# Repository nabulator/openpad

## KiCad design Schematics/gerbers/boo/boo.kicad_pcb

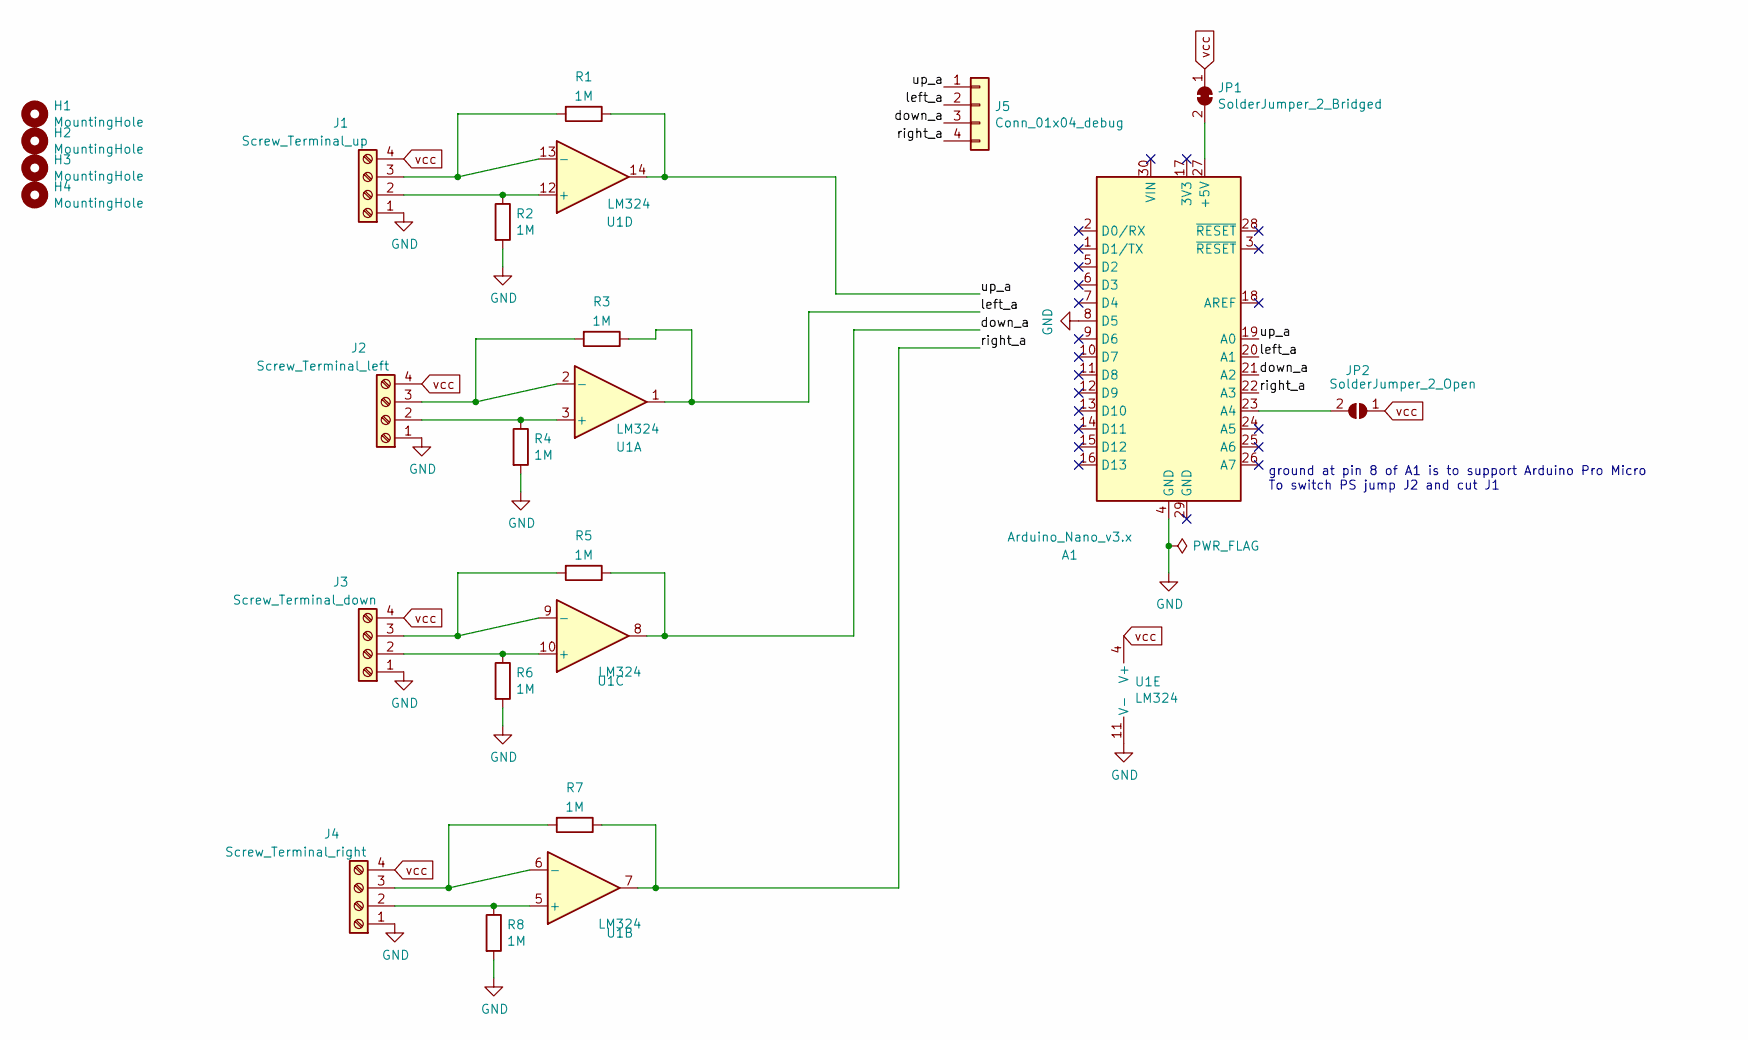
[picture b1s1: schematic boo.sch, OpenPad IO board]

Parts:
A1: Arduino_Nano_v3.x; Arduino_Nano_WithMountingHoles
H1, H2, H3, H4: MountingHole; MountingHole_6.4mm_M6
J1: Screw_Terminal_up; PinHeader_1x04_P2.54mm_Vertical
J2: Screw_Terminal_left; PinHeader_1x04_P2.54mm_Vertical
J3: Screw_Terminal_down; PinHeader_1x04_P2.54mm_Vertical
J4: Screw_Terminal_right; PinHeader_1x04_P2.54mm_Vertical
J5: Conn_01x04_debug; JST_XH_B4B-XH-A_1x04_P2.50mm_Vertical
JP1: SolderJumper_2_Bridged; SolderJumper-2_P1.3mm_Bridged2Bar_Pad1.0x1.5mm
JP2: SolderJumper_2_Open; SolderJumper-2_P1.3mm_Open_Pad1.0x1.5mm
R1, R2, R3, R4, R5, R6, R7, R8: 1M; R_Axial_DIN0207_L6.3mm_D2.5mm_P10.16mm_Horizontal
U1: LM324; DIP-14_W7.62mm_Socket

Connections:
/down_a: A1.21 (A2), J5.3, R5.1, U1.8
/left_a: A1.20 (A1), J5.2, R3.1, U1.1
/right_a: A1.22 (A3), J5.4, R7.1, U1.7
/up_a: A1.19 (A0), J5.1, R1.1, U1.14
GND: A1.4 (GND), A1.8 (D5), J1.1, J2.1, J3.1, J4.1, R2.2, R4.2, R6.2, R8.2, U1.11 (V-)
unnamed: A1.23 (A4), JP2.2 (B)
unnamed: A1.27 (+5V), JP1.2 (B)
unnamed: J1.2, R2.1, U1.12 (+)
unnamed: J1.3, R1.2, U1.13 (-)
unnamed: J2.2, R4.1, U1.3 (+)
unnamed: J2.3, R3.2, U1.2 (-)
unnamed: J3.2, R6.1, U1.10 (+)
unnamed: J3.3, R5.2, U1.9 (-)
unnamed: J4.2, R8.1, U1.5 (+)
unnamed: J4.3, R7.2, U1.6 (-)
vcc: J1.4, J2.4, J3.4, J4.4, JP1.1 (A), JP2.1 (A), U1.4 (V+)

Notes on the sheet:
ground at pin 8 of A1 is to support Arduino Pro Micro To switch PS jump J2 and cut J1

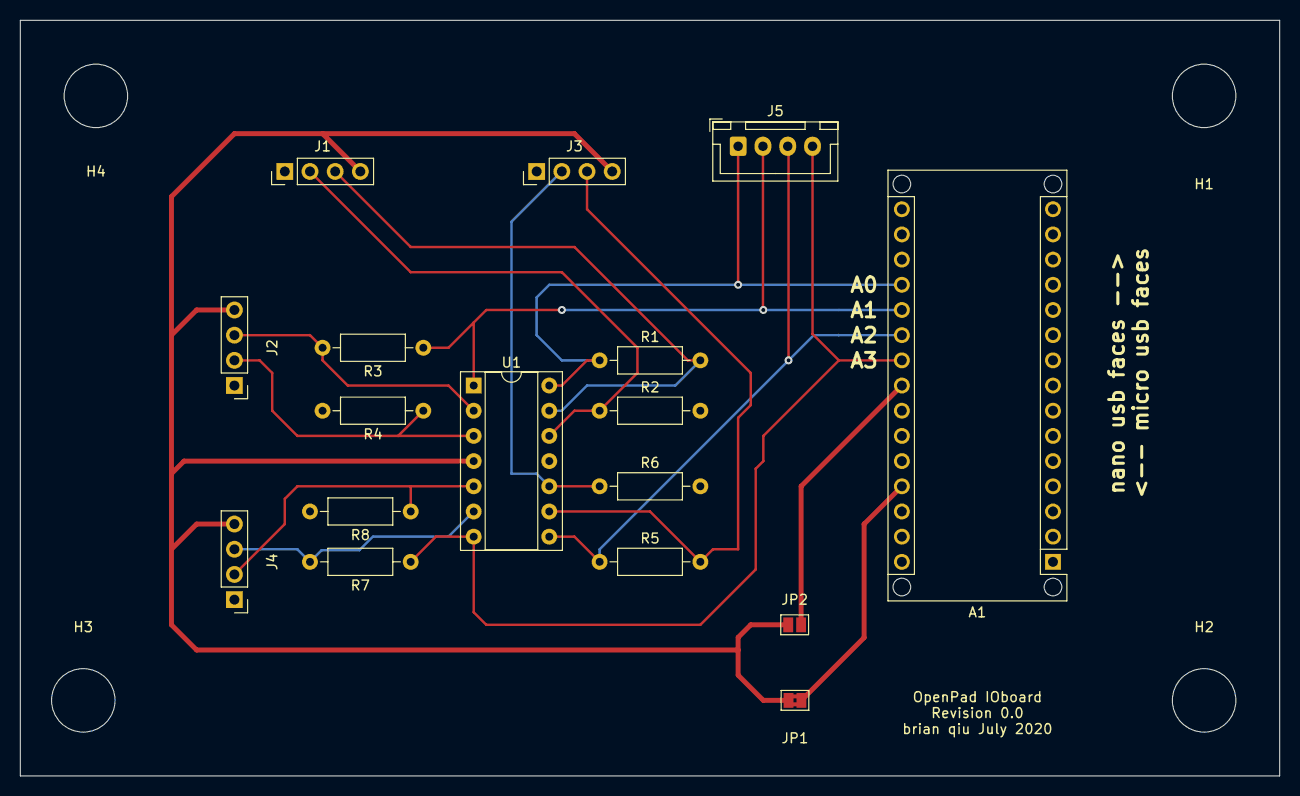
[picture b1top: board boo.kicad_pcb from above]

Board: 2 copper layers, 127.0 x 76.2 mm, 21 parts (0 on the bottom side), 16 nets.

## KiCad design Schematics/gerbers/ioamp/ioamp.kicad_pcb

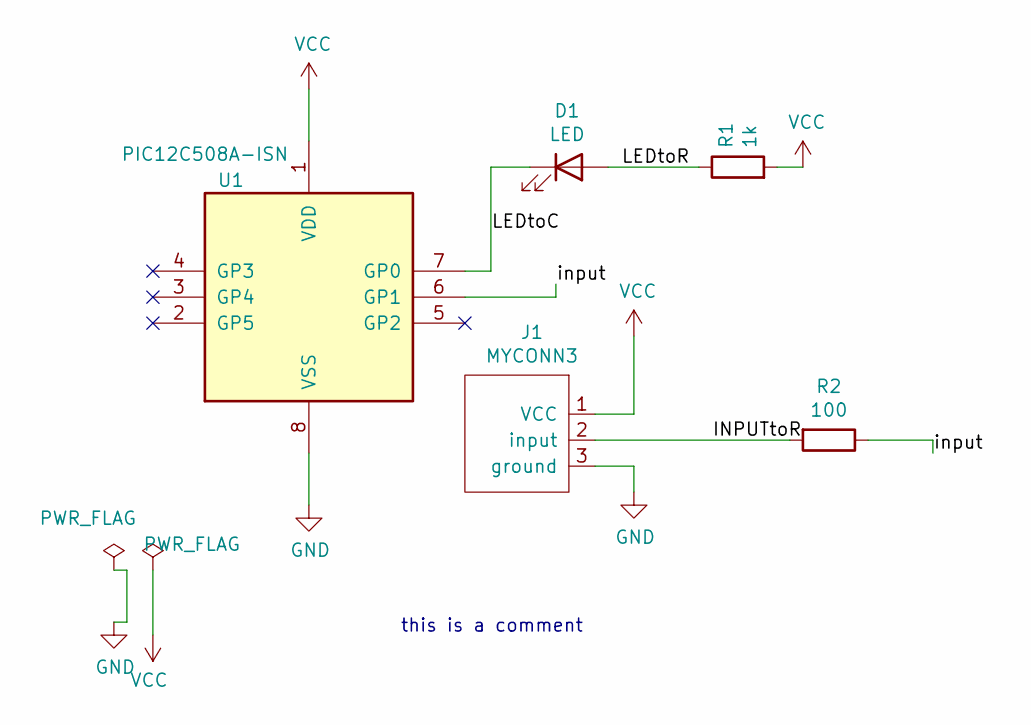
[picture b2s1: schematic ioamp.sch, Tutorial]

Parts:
D1: LED; LED_D5.0mm
J1: MYCONN3; Banana_Jack_3Pin
R1: 1k; R_Axial_DIN0207_L6.3mm_D2.5mm_P2.54mm_Vertical
R2: 100; R_Axial_DIN0207_L6.3mm_D2.5mm_P2.54mm_Vertical
U1: PIC12C508A-ISN; DIP-8_W7.62mm

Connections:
/INPUTtoR: J1.2 (input), R2.2
/LEDtoC: D1.1 (K), U1.7 (GP0)
/LEDtoR: D1.2 (A), R1.1
/input: R2.1, U1.6 (GP1)
GND: J1.3 (ground), U1.8 (VSS)
VCC: J1.1 (VCC), R1.2, U1.1 (VDD)

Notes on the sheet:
this is a comment

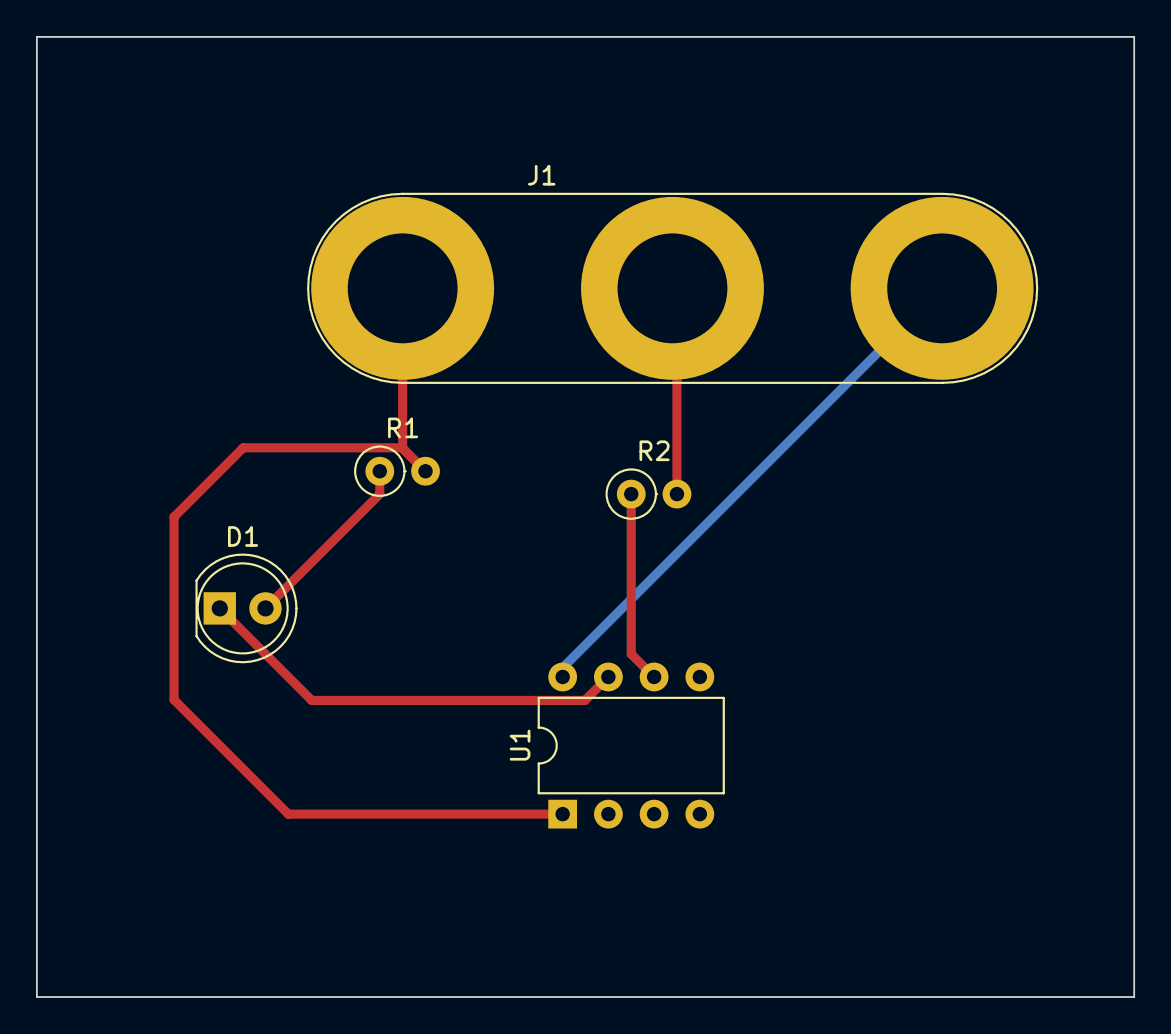
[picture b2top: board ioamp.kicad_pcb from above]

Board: 2 copper layers, 61.0 x 53.3 mm, 5 parts (0 on the bottom side), 6 nets.

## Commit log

2020-07-23 modified build for my negative clock edge sensors + LEDs
2020-07-23 flash script for rapid prototyping
2020-07-23 my first PCB layout! :D
